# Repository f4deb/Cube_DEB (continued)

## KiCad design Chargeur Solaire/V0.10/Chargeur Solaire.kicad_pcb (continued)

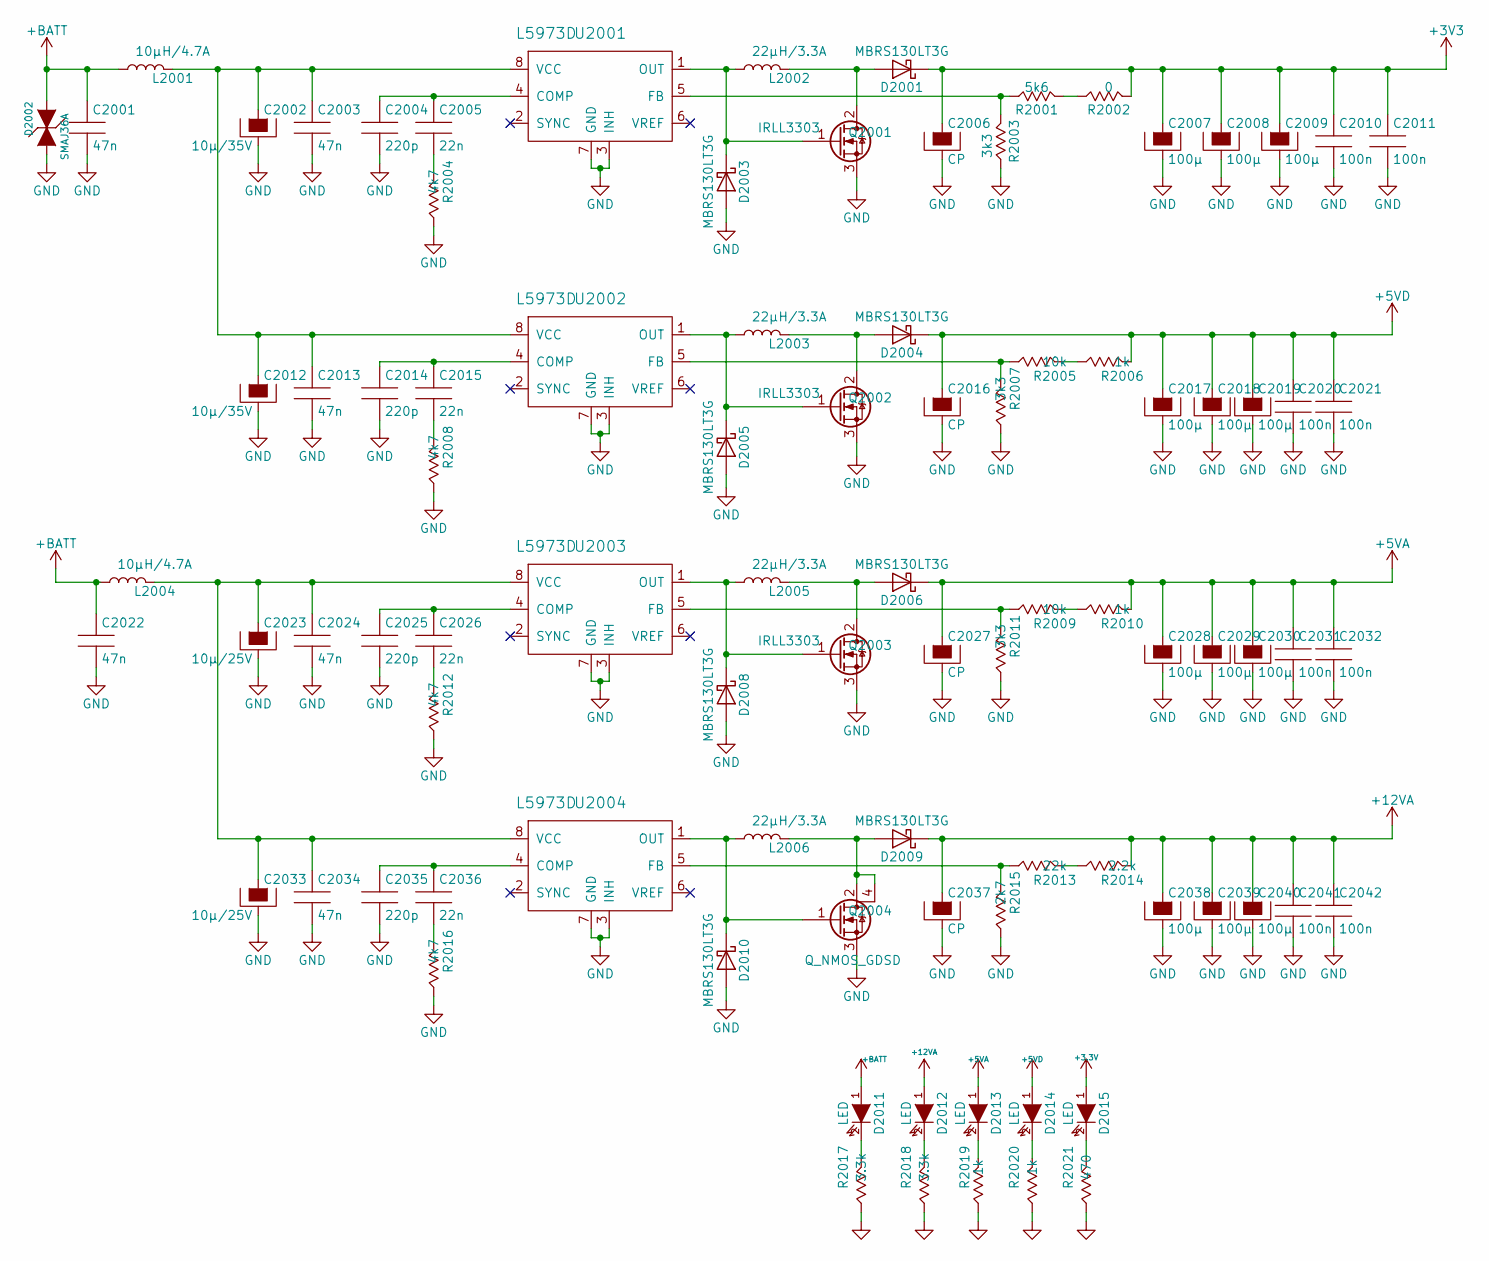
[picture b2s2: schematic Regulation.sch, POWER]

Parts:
C2001, C2003, C2013, C2022, C2024, C2034: 47n; C_0603
C2002, C2012: 10µ/35V; Tantalum_Case-D_EIA-7343-31_Reflow
C2004, C2014, C2025, C2035: 220p; C_0603
C2005, C2015, C2026, C2036: 22n; C_0603
C2006, C2016, C2027, C2037: CP; Tantalum_Case-D_EIA-7343-31_Reflow
C2007, C2008, C2009, C2017, C2018, C2019, C2028, C2029, C2030, C2038, C2039, C2040: 100µ; Tantalum_Case-A_EIA-3216-18_Reflow
C2010, C2011, C2020, C2021, C2031, C2032, C2041, C2042: 100n; C_0603
C2023, C2033: 10µ/25V; Tantalum_Case-D_EIA-7343-31_Reflow
D2001, D2004, D2005, D2006, D2008, D2009, D2010: MBRS130LT3G; SMC_Standard
D2002: SMAJ36A; SMC_Standard
D2003: MBRS130LT3G; DO-214AB
D2011, D2012, D2013, D2014, D2015: LED; LED_0603
L2001, L2004: 10µH/4.7A; Self_30_BiTech
L2002, L2003, L2005, L2006: 22µH/3.3A; Self_30_BiTech
Q2001, Q2002, Q2003: IRLL3303; SOT-223
Q2004: Q_NMOS_GDSD; SOT-223
R2001: 5k6; R_0603
R2002: 0; R_0603
R2003, R2007, R2011: 3k3; R_0603
R2004, R2008, R2012, R2016: 4k7; R_0603
R2005, R2009: 10k; R_0603
R2006, R2010, R2019, R2020: 1k; R_0603
R2013: 22k; R_0603
R2014: 2.2k; R_0603
R2015: 2k7; R_0603
R2017, R2018: 3.3k; R_0603
R2021: 470; R_0603
U2001, U2002, U2003, U2004: L5973D; SOIC-8_3.9x4.9mm_Pitch1.27mm

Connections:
+5VA: C2027.1, C2028.1, C2029.1, C2030.1, C2031.1, C2032.1, D2006.1 (K), D2013.1 (A), R2010.1; also elsewhere on the board
+5VD: C2016.1, C2017.1, C2018.1, C2019.1, C2020.1, C2021.1, D2004.1 (K), D2014.1 (A), R2006.1; also elsewhere on the board
+12VA: C2037.1, C2038.1, C2039.1, C2040.1, C2041.1, C2042.1, D2009.1 (K), D2012.1 (A), R2014.1; also elsewhere on the board
+BATT: C2001.1, C2022.1, D2002.2 (K), D2011.1 (A), L2001.1, L2004.1; also elsewhere on the board
GND: C2001.2, C2002.2, C2003.2, C2004.2, C2006.2, C2007.2, C2008.2, C2009.2, C2010.2, C2011.2, C2012.2, C2013.2, C2014.2, C2016.2, C2017.2, C2018.2, C2019.2, C2020.2, C2021.2, C2022.2, C2023.2, C2024.2, C2025.2, C2027.2, C2028.2, C2029.2, C2030.2, C2031.2, C2032.2, C2033.2, C2034.2, C2035.2, C2037.2, C2038.2, C2039.2, C2040.2, C2041.2, C2042.2, D2002.1 (A), D2003.2 (A), D2005.2 (A), D2008.2 (A), D2010.2 (A), Q2001.3 (S), Q2002.3 (S), Q2003.3 (S), Q2004.3 (S), R2003.2, R2004.2, R2007.2, R2008.2, R2011.2, R2012.2, R2015.2, R2016.2, R2017.2, R2018.2, R2019.2, R2020.2, R2021.2, U2001.3 (INH), U2001.7 (GND), U2002.3 (INH), U2002.7 (GND), U2003.3 (INH), U2003.7 (GND), U2004.3 (INH), U2004.7 (GND); also elsewhere on the board
unnamed: C2002.1, C2003.1, C2012.1, C2013.1, L2001.2, U2001.8 (VCC), U2002.8 (VCC)
unnamed: C2004.1, C2005.1, U2001.4 (COMP)
unnamed: C2005.2, R2004.1
unnamed: C2014.1, C2015.1, U2002.4 (COMP)
unnamed: C2015.2, R2008.1
unnamed: C2023.1, C2024.1, C2033.1, C2034.1, L2004.2, U2003.8 (VCC), U2004.8 (VCC)
unnamed: C2025.1, C2026.1, U2003.4 (COMP)
unnamed: C2026.2, R2012.1
unnamed: C2035.1, C2036.1, U2004.4 (COMP)
unnamed: C2036.2, R2016.1
unnamed: D2001.2 (A), L2002.2, Q2001.2 (D)
unnamed: D2003.1 (K), L2002.1, Q2001.1 (G), U2001.1 (OUT)
unnamed: D2004.2 (A), L2003.2, Q2002.2 (D)
unnamed: D2005.1 (K), L2003.1, Q2002.1 (G), U2002.1 (OUT)
unnamed: D2006.2 (A), L2005.2, Q2003.2 (D)
unnamed: D2008.1 (K), L2005.1, Q2003.1 (G), U2003.1 (OUT)
unnamed: D2009.2 (A), L2006.2, Q2004.2 (D), Q2004.4 (D)
unnamed: D2010.1 (K), L2006.1, Q2004.1 (G), U2004.1 (OUT)
unnamed: D2011.2 (K), R2017.1
unnamed: D2012.2 (K), R2018.1
unnamed: D2013.2 (K), R2019.1
unnamed: D2014.2 (K), R2020.1
unnamed: D2015.2 (K), R2021.1
unnamed: R2001.1, R2002.2
unnamed: R2001.2, R2003.1, U2001.5 (FB)
unnamed: R2005.1, R2006.2
unnamed: R2005.2, R2007.1, U2002.5 (FB)
unnamed: R2009.1, R2010.2
unnamed: R2009.2, R2011.1, U2003.5 (FB)
unnamed: R2013.1, R2014.2
unnamed: R2013.2, R2015.1, U2004.5 (FB)

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
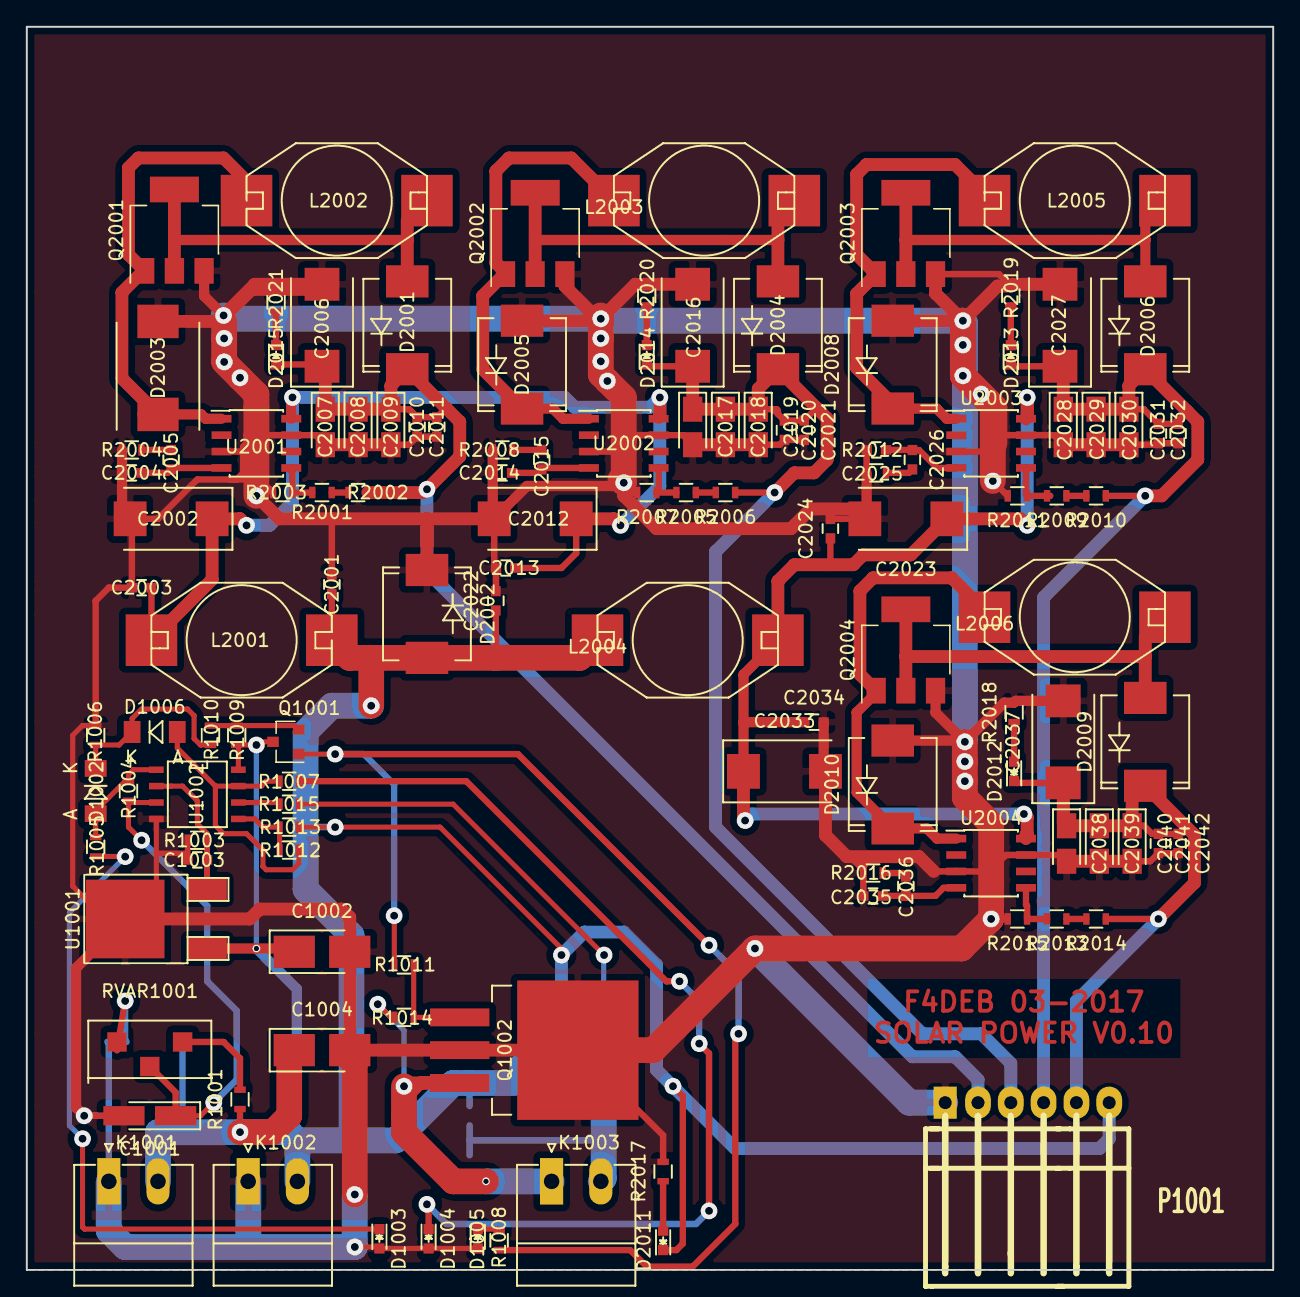
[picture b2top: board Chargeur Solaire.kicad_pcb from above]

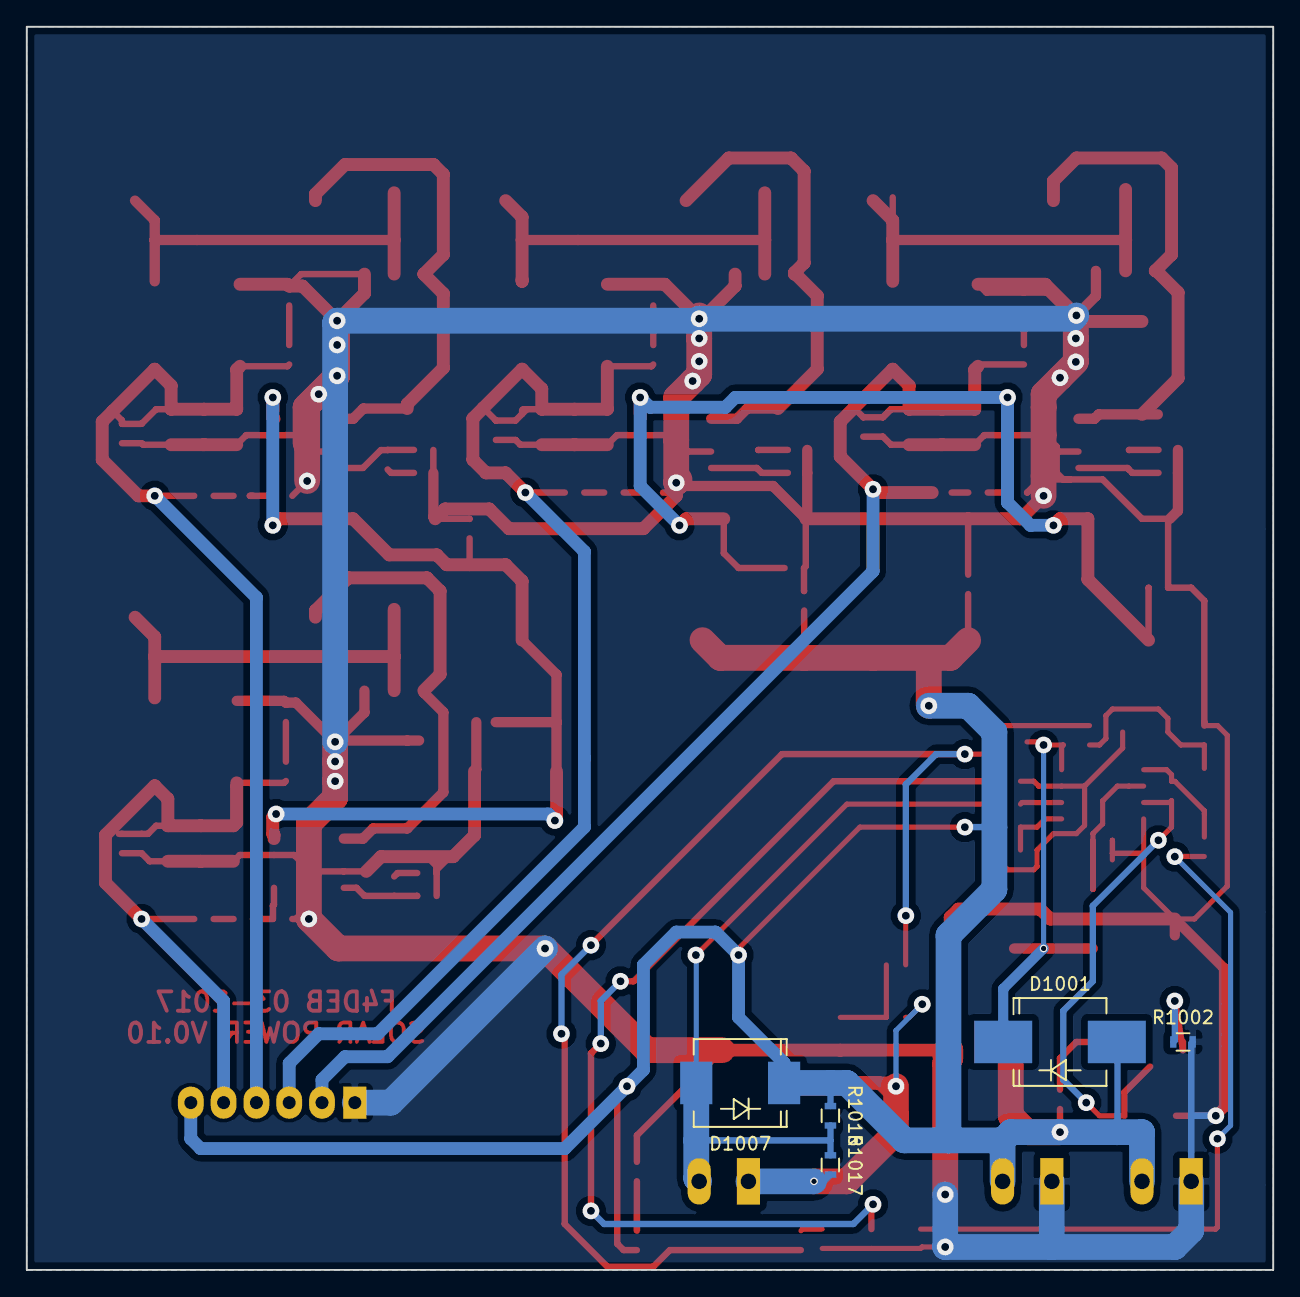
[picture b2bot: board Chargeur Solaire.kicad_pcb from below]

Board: 2 copper layers, 96.5 x 96.3 mm, 128 parts (5 on the bottom side), 55 nets.

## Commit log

2017-03-22 Debut
2019-02-16 INIT
